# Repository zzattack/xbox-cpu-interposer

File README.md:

# Repository overview
In this repository schematics, layout and gerber files are shared for the recreation of an interposer PCB allowing upgraded Intel CPUs to be used on the original Xbox console. The designs are made in KiCAD.

# Background
Back in 2003 the Taiwanese company FRIENDTECH came up with methods to upgrade computer systems with faster CPUs, and the original Xbox was among the devices for which they offered an upgrade path. Details of their solution can be found in their patent application https://patents.google.com/patent/US20050282621A1/en.

This _interposer board_ follows the same schematic, minus the poorly functioning clock reduction circuitry, and with the BGA footprint positioned to allow use of the original heatsink mounting holes.

# Contact
I can be contacted at frank@zzattack.org if you're looking to obtain PCBs or CPUs.

# Attribution
This board is a recreation of the original FRIENDTECH design. Revision 1 was a board-level clone of original design through intermediate clones by 'trusty', 'N64freak' and 'Kekule'. Revisions 2 and 3 are re-routed from scratch, inspired by pictures of a similar board with cleaner layout by @gaasedelen, who also kindly assisted in finding issues with early board revisions.

# Installation guide
See [guide](https://github.com/zzattack/xbox-cpu-interposer/blob/main/guide.md).

# Status
Full schematic and PCB are routed. Gerber files are available in the Github releases overview.
Revision 3.2 and onwards should be working correctly.
Prior revisions require PCB modifications and should be avoided.

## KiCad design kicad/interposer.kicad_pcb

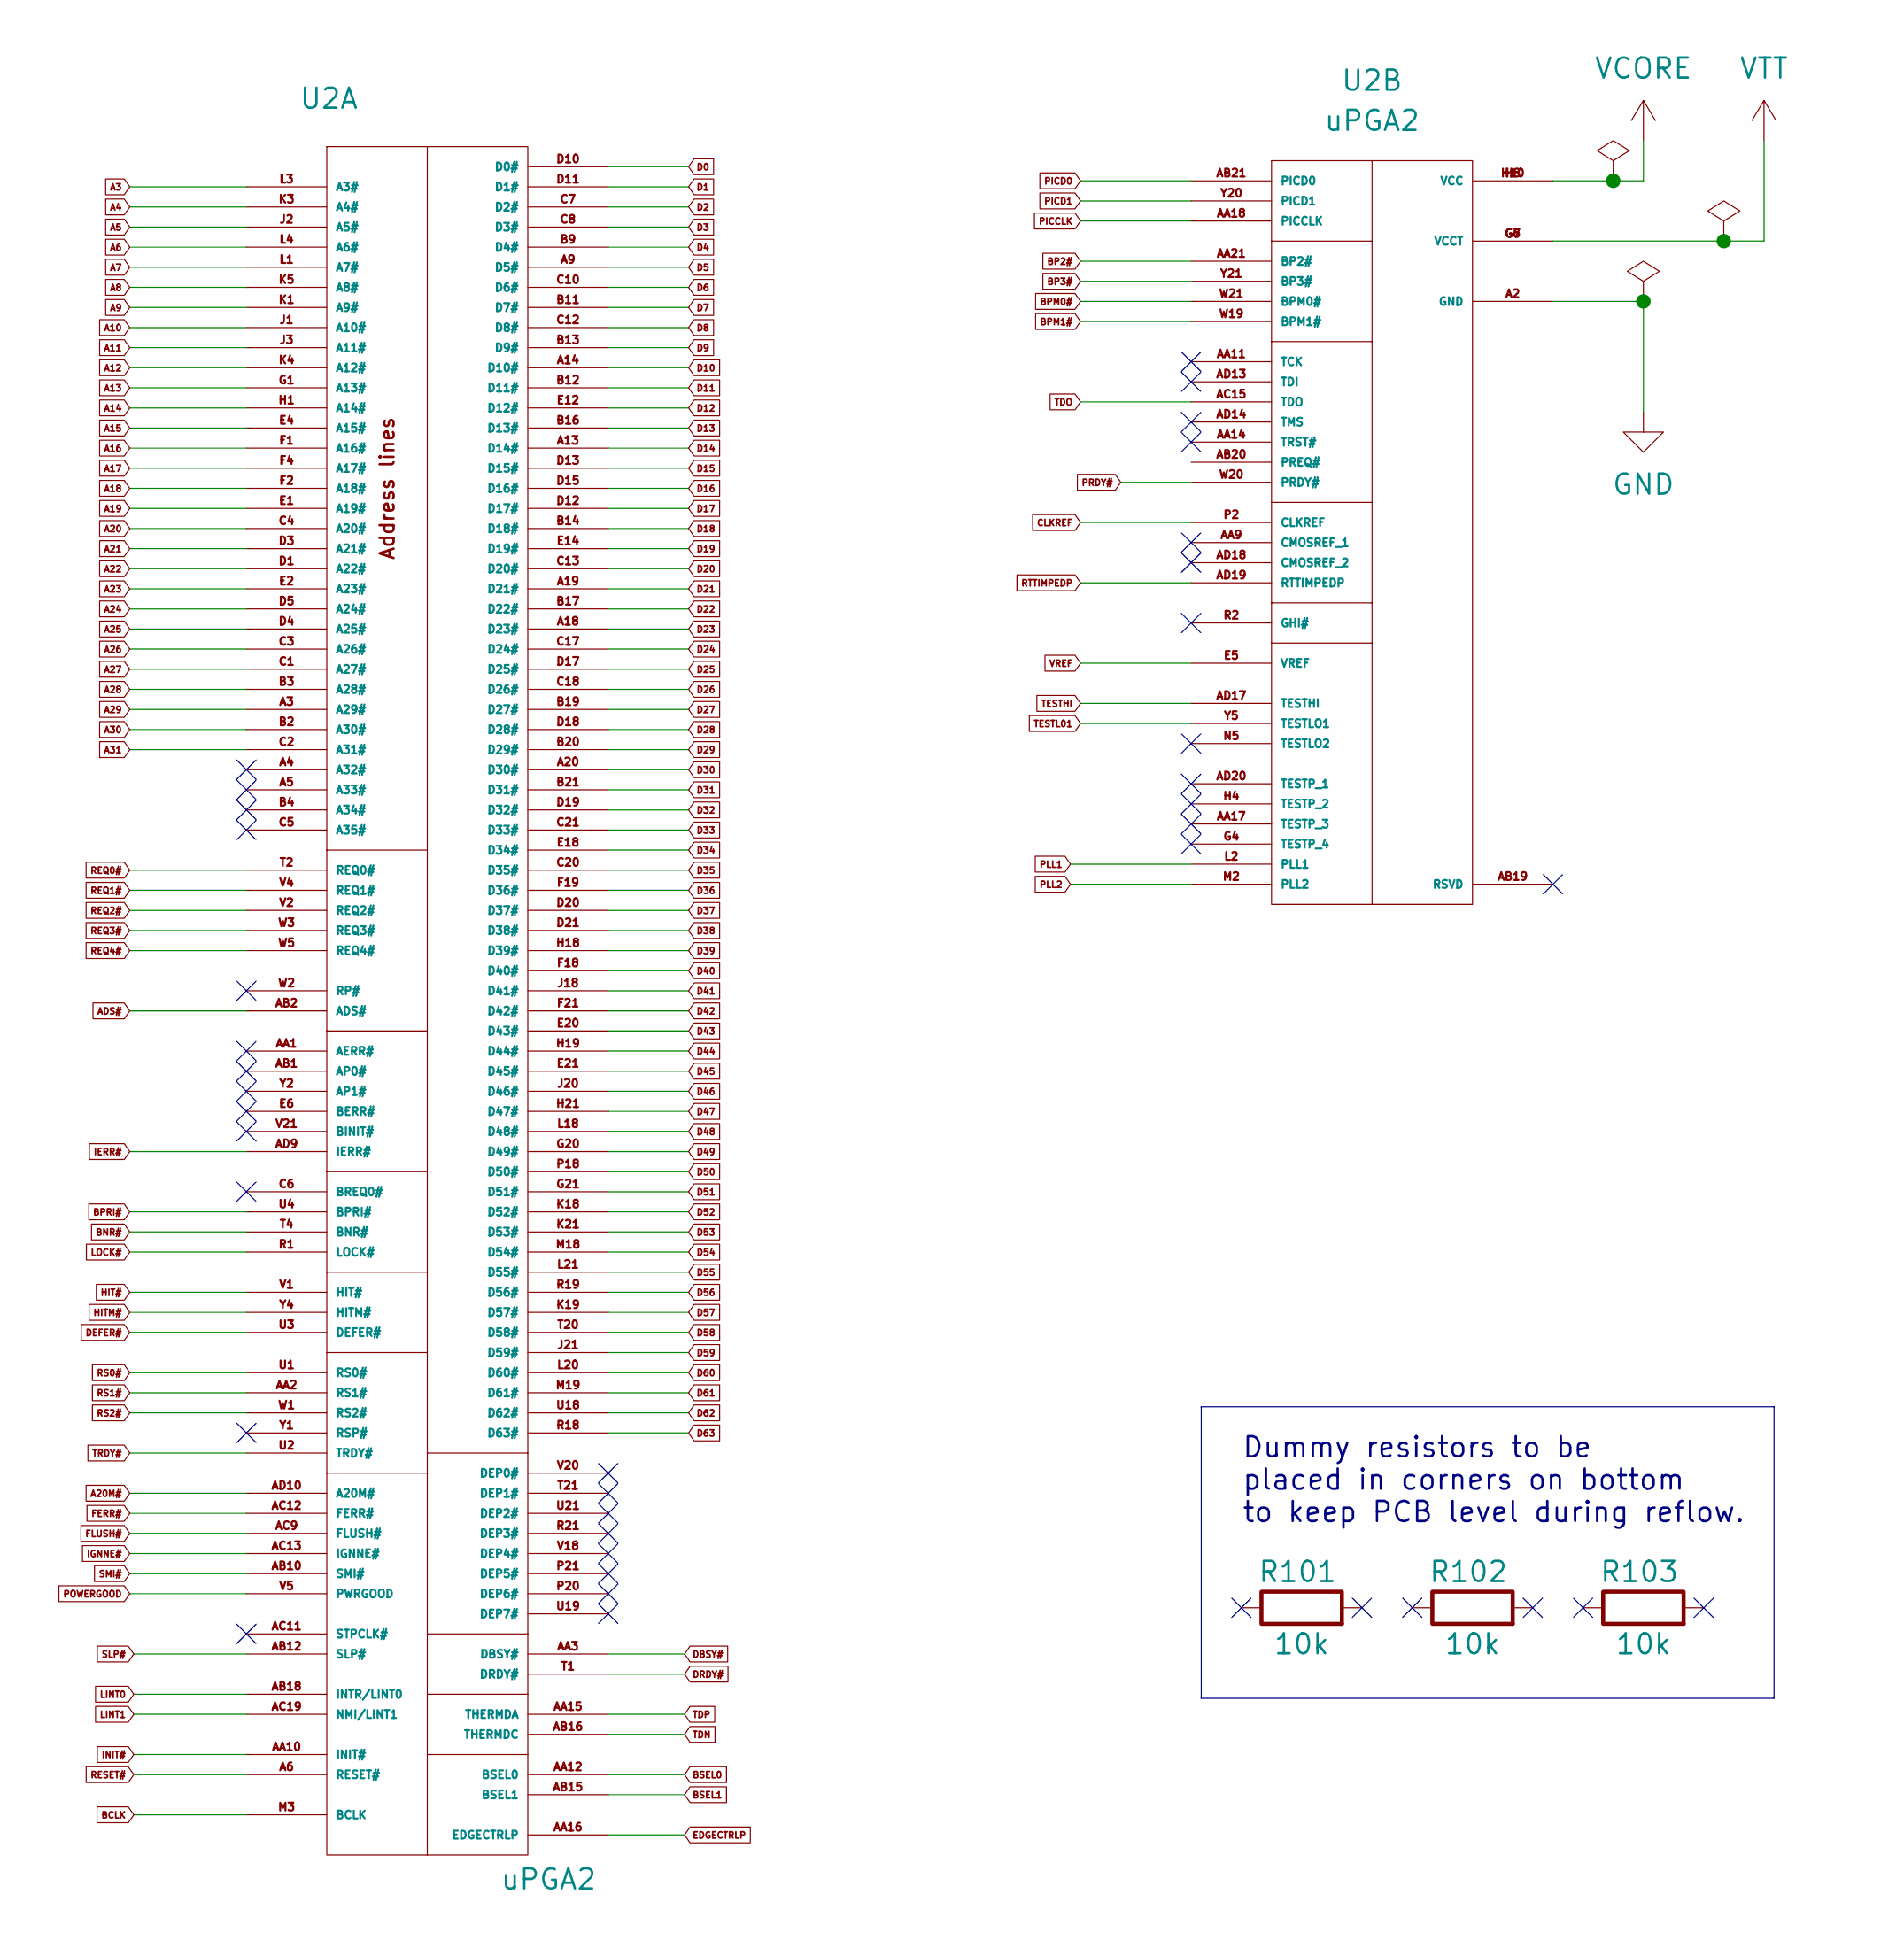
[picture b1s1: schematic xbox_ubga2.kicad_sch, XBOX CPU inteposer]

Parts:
R101, R102, R103: 10k; R_0603_1608Metric
U2: uPGA2; uBGA495-mirrored

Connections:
A3: U2.L3 (A3#); also elsewhere on the board
A4: U2.K3 (A4#); also elsewhere on the board
A5: U2.J2 (A5#); also elsewhere on the board
A6: U2.L4 (A6#); also elsewhere on the board
A7: U2.L1 (A7#); also elsewhere on the board
A8: U2.K5 (A8#); also elsewhere on the board
A9: U2.K1 (A9#); also elsewhere on the board
A10: U2.J1 (A10#); also elsewhere on the board
A11: U2.J3 (A11#); also elsewhere on the board
A12: U2.K4 (A12#); also elsewhere on the board
A13: U2.G1 (A13#); also elsewhere on the board
A14: U2.H1 (A14#); also elsewhere on the board
A15: U2.E4 (A15#); also elsewhere on the board
A16: U2.F1 (A16#); also elsewhere on the board
A17: U2.F4 (A17#); also elsewhere on the board
A18: U2.F2 (A18#); also elsewhere on the board
A19: U2.E1 (A19#); also elsewhere on the board
A20: U2.C4 (A20#); also elsewhere on the board
A20M#: U2.AD10 (A20M#); also elsewhere on the board
A21: U2.D3 (A21#); also elsewhere on the board
A22: U2.D1 (A22#); also elsewhere on the board
A23: U2.E2 (A23#); also elsewhere on the board
A24: U2.D5 (A24#); also elsewhere on the board
A25: U2.D4 (A25#); also elsewhere on the board
A26: U2.C3 (A26#); also elsewhere on the board
A27: U2.C1 (A27#); also elsewhere on the board
A28: U2.B3 (A28#); also elsewhere on the board
A29: U2.A3 (A29#); also elsewhere on the board
A30: U2.B2 (A30#); also elsewhere on the board
A31: U2.C2 (A31#); also elsewhere on the board
ADS#: U2.AB2 (ADS#); also elsewhere on the board
BCLK: U2.M3 (BCLK); also elsewhere on the board
BNR#: U2.T4 (BNR#); also elsewhere on the board
BP2#: U2.AA21 (BP2#); also elsewhere on the board
BP3#: U2.Y21 (BP3#); also elsewhere on the board
BPM0#: U2.W21 (BPM0#); also elsewhere on the board
BPM1#: U2.W19 (BPM1#); also elsewhere on the board
BPRI#: U2.U4 (BPRI#); also elsewhere on the board
BSEL0: U2.AA12 (BSEL0); also elsewhere on the board
BSEL1: U2.AB15 (BSEL1); also elsewhere on the board
CLKREF: U2.P2 (CLKREF); also elsewhere on the board
D0: U2.D10 (D0#); also elsewhere on the board
D1: U2.D11 (D1#); also elsewhere on the board
D2: U2.C7 (D2#); also elsewhere on the board
D3: U2.C8 (D3#); also elsewhere on the board
D4: U2.B9 (D4#); also elsewhere on the board
D5: U2.A9 (D5#); also elsewhere on the board
D6: U2.C10 (D6#); also elsewhere on the board
D7: U2.B11 (D7#); also elsewhere on the board
D8: U2.C12 (D8#); also elsewhere on the board
D9: U2.B13 (D9#); also elsewhere on the board
D10: U2.A14 (D10#); also elsewhere on the board
D11: U2.B12 (D11#); also elsewhere on the board
D12: U2.E12 (D12#); also elsewhere on the board
D13: U2.B16 (D13#); also elsewhere on the board
D14: U2.A13 (D14#); also elsewhere on the board
D15: U2.D13 (D15#); also elsewhere on the board
D16: U2.D15 (D16#); also elsewhere on the board
D17: U2.D12 (D17#); also elsewhere on the board
D18: U2.B14 (D18#); also elsewhere on the board
D19: U2.E14 (D19#); also elsewhere on the board
D20: U2.C13 (D20#); also elsewhere on the board
D21: U2.A19 (D21#); also elsewhere on the board
D22: U2.B17 (D22#); also elsewhere on the board
D23: U2.A18 (D23#); also elsewhere on the board
D24: U2.C17 (D24#); also elsewhere on the board
D25: U2.D17 (D25#); also elsewhere on the board
D26: U2.C18 (D26#); also elsewhere on the board
D27: U2.B19 (D27#); also elsewhere on the board
D28: U2.D18 (D28#); also elsewhere on the board
D29: U2.B20 (D29#); also elsewhere on the board
D30: U2.A20 (D30#); also elsewhere on the board
D31: U2.B21 (D31#); also elsewhere on the board
D32: U2.D19 (D32#); also elsewhere on the board
D33: U2.C21 (D33#); also elsewhere on the board
D34: U2.E18 (D34#); also elsewhere on the board
D35: U2.C20 (D35#); also elsewhere on the board
D36: U2.F19 (D36#); also elsewhere on the board
D37: U2.D20 (D37#); also elsewhere on the board
D38: U2.D21 (D38#); also elsewhere on the board
D39: U2.H18 (D39#); also elsewhere on the board
D40: U2.F18 (D40#); also elsewhere on the board
D41: U2.J18 (D41#); also elsewhere on the board
D42: U2.F21 (D42#); also elsewhere on the board
D43: U2.E20 (D43#); also elsewhere on the board
D44: U2.H19 (D44#); also elsewhere on the board
D45: U2.E21 (D45#); also elsewhere on the board
D46: U2.J20 (D46#); also elsewhere on the board
D47: U2.H21 (D47#); also elsewhere on the board
D48: U2.L18 (D48#); also elsewhere on the board
D49: U2.G20 (D49#); also elsewhere on the board
D50: U2.P18 (D50#); also elsewhere on the board
D51: U2.G21 (D51#); also elsewhere on the board
D52: U2.K18 (D52#); also elsewhere on the board
D53: U2.K21 (D53#); also elsewhere on the board
D54: U2.M18 (D54#); also elsewhere on the board
D55: U2.L21 (D55#); also elsewhere on the board
D56: U2.R19 (D56#); also elsewhere on the board
D57: U2.K19 (D57#); also elsewhere on the board
D58: U2.T20 (D58#); also elsewhere on the board
D59: U2.J21 (D59#); also elsewhere on the board
D60: U2.L20 (D60#); also elsewhere on the board
D61: U2.M19 (D61#); also elsewhere on the board
D62: U2.U18 (D62#); also elsewhere on the board
D63: U2.R18 (D63#); also elsewhere on the board
DBSY#: U2.AA3 (DBSY#); also elsewhere on the board
DEFER#: U2.U3 (DEFER#); also elsewhere on the board
DRDY#: U2.T1 (DRDY#); also elsewhere on the board
EDGECTRLP: U2.AA16 (EDGECTRLP); also elsewhere on the board
FERR#: U2.AC12 (FERR#); also elsewhere on the board
FLUSH#: U2.AC9 (FLUSH#); also elsewhere on the board
GND: U2.A2 (GND), U2.A7 (GND), U2.A8 (GND), U2.A12 (GND), U2.A21 (GND), U2.AA4 (GND), U2.AA13 (GND), U2.AA20 (GND), U2.AB3 (GND), U2.AB5 (GND), U2.AB9 (GND), U2.AB11 (GND), U2.AB13 (GND), U2.AB14 (GND), U2.AB17 (GND), U2.AC1 (GND), U2.AC2 (GND), U2.AC5 (GND), U2.AC10 (GND), U2.AC14 (GND), U2.AC16 (GND), U2.AC18 (GND), U2.AC21 (GND), U2.AD1 (GND), U2.AD5 (GND), U2.AD16 (GND), U2.AD21 (GND), U2.B1 (GND), U2.B5 (GND), U2.B6 (GND), U2.B7 (GND), U2.B8 (GND), U2.B10 (GND), U2.B15 (GND), U2.B18 (GND), U2.C9 (GND), U2.C11 (GND), U2.C15 (GND), U2.C16 (GND), U2.C19 (GND), U2.D2 (GND), U2.D6 (GND), U2.D7 (GND), U2.D9 (GND), U2.E3 (GND), U2.E7 (GND), U2.E8 (GND), U2.E9 (GND), U2.E10 (GND), U2.E11 (GND), U2.E13 (GND), U2.E19 (GND), U2.F3 (GND), U2.F6 (GND), U2.F7 (GND), U2.F8 (GND), U2.F9 (GND), U2.F10 (GND), U2.F11 (GND), U2.F12 (GND), U2.F13 (GND), U2.F14 (GND), U2.F15 (GND), U2.F16 (GND), U2.F20 (GND), U2.G3 (GND), U2.G19 (GND), U2.H2 (GND), U2.H7 (GND), U2.H9 (GND), U2.H11 (GND), U2.H13 (GND), U2.H15 (GND), U2.H20 (GND), U2.J4 (GND), U2.J8 (GND), U2.J10 (GND), U2.J12 (GND), U2.J14 (GND), U2.J16 (GND), U2.J19 (GND), U2.K2 (GND), U2.K7 (GND), U2.K9 (GND), U2.K11 (GND), U2.K13 (GND), U2.K15 (GND), U2.K20 (GND), U2.L5 (GND), U2.L8 (GND), U2.L10 (GND), U2.L12 (GND), U2.L14 (GND), U2.L16 (GND), U2.L19 (GND), U2.M7 (GND), U2.M9 (GND), U2.M11 (GND), U2.M13 (GND), U2.M15 (GND), U2.M20 (GND), U2.N2 (GND), U2.N3 (GND), U2.N4 (GND), U2.N8 (GND), U2.N10 (GND), U2.N12 (GND), U2.N14 (GND), U2.N16 (GND), U2.N18 (GND), U2.N19 (GND), U2.N20 (GND), U2.P5 (GND), U2.P7 (GND), U2.P9 (GND), U2.P11 (GND), U2.P13 (GND), U2.P15 (GND), U2.P19 (GND), U2.R3 (GND), U2.R4 (GND), U2.R5 (GND), U2.R8 (GND), U2.R10 (GND), U2.R12 (GND), U2.R14 (GND), U2.R16 (GND), U2.R20 (GND), U2.T3 (GND), U2.T5 (GND), U2.T7 (GND), U2.T9 (GND), U2.T11 (GND), U2.T13 (GND), U2.T15 (GND), U2.T18 (GND), U2.T19 (GND), U2.U8 (GND), U2.U10 (GND), U2.U12 (GND), U2.U14 (GND), U2.U16 (GND), U2.U20 (GND), U2.V3 (GND), U2.V19 (GND), U2.W4 (GND), U2.W18 (GND), U2.Y3 (GND), U2.Y9 (GND), U2.Y10 (GND), U2.Y11 (GND), U2.Y12 (GND), U2.Y13 (GND), U2.Y14 (GND), U2.Y15 (GND), U2.Y16 (GND), U2.Y19 (GND); also elsewhere on the board
HIT#: U2.V1 (HIT#); also elsewhere on the board
HITM#: U2.Y4 (HITM#); also elsewhere on the board
IERR#: U2.AD9 (IERR#); also elsewhere on the board
IGNNE#: U2.AC13 (IGNNE#); also elsewhere on the board
INIT#: U2.AA10 (INIT#); also elsewhere on the board
LINT0: U2.AB18 (INTR/LINT0); also elsewhere on the board
LINT1: U2.AC19 (NMI/LINT1); also elsewhere on the board
LOCK#: U2.R1 (LOCK#); also elsewhere on the board
PICCLK: U2.AA18 (PICCLK); also elsewhere on the board
PICD0: U2.AB21 (PICD0); also elsewhere on the board
PICD1: U2.Y20 (PICD1); also elsewhere on the board
PLL1: U2.L2 (PLL1); also elsewhere on the board
PLL2: U2.M2 (PLL2); also elsewhere on the board
POWERGOOD: U2.V5 (PWRGOOD); also elsewhere on the board
PRDY#: U2.W20 (PRDY#); also elsewhere on the board
REQ0#: U2.T2 (REQ0#); also elsewhere on the board
REQ1#: U2.V4 (REQ1#); also elsewhere on the board
REQ2#: U2.V2 (REQ2#); also elsewhere on the board
REQ3#: U2.W3 (REQ3#); also elsewhere on the board
REQ4#: U2.W5 (REQ4#); also elsewhere on the board
RESET#: U2.A6 (RESET#); also elsewhere on the board
RS0#: U2.U1 (RS0#); also elsewhere on the board
RS1#: U2.AA2 (RS1#); also elsewhere on the board
RS2#: U2.W1 (RS2#); also elsewhere on the board
RTTIMPEDP: U2.AD19 (RTTIMPEDP); also elsewhere on the board
SLP#: U2.AB12 (SLP#); also elsewhere on the board
SMI#: U2.AB10 (SMI#); also elsewhere on the board
TDN: U2.AB16 (THERMDC); also elsewhere on the board
TDO: U2.AC15 (TDO); also elsewhere on the board
TDP: U2.AA15 (THERMDA); also elsewhere on the board
TESTHI: U2.AD17 (TESTHI); also elsewhere on the board
TESTL01: U2.Y5 (TESTLO1); also elsewhere on the board
TRDY#: U2.U2 (TRDY#); also elsewhere on the board
VCORE: U2.H8 (VCC), U2.H10 (VCC), U2.H12 (VCC), U2.H14 (VCC), U2.H16 (VCC), U2.J7 (VCC), U2.J9 (VCC), U2.J11 (VCC), U2.J13 (VCC), U2.J15 (VCC), U2.K8 (VCC), U2.K10 (VCC), U2.K12 (VCC), U2.K14 (VCC), U2.K16 (VCC), U2.L7 (VCC), U2.L9 (VCC), U2.L11 (VCC), U2.L13 (VCC), U2.L15 (VCC), U2.M8 (VCC), U2.M10 (VCC), U2.M12 (VCC), U2.M14 (VCC), U2.M16 (VCC), U2.N7 (VCC), U2.N9 (VCC), U2.N11 (VCC), U2.N13 (VCC), U2.N15 (VCC), U2.P1 (VCC), U2.P8 (VCC), U2.P10 (VCC), U2.P12 (VCC), U2.P14 (VCC), U2.P16 (VCC), U2.R7 (VCC), U2.R9 (VCC), U2.R11 (VCC), U2.R13 (VCC), U2.R15 (VCC), U2.T8 (VCC), U2.T10 (VCC), U2.T12 (VCC), U2.T14 (VCC), U2.T16 (VCC), U2.U7 (VCC), U2.U9 (VCC), U2.U11 (VCC), U2.U13 (VCC), U2.U15 (VCC); also elsewhere on the board
VREF: U2.E5 (VREF), U2.E16 (VREF), U2.E17 (VREF), U2.F5 (VREF), U2.F17 (VREF), U2.U5 (VREF), U2.Y17 (VREF), U2.Y18 (VREF); also elsewhere on the board
VTT: U2.AA6 (VCCT), U2.AA7 (VCCT), U2.AA8 (VCCT), U2.AB6 (VCCT), U2.AB7 (VCCT), U2.AB8 (VCCT), U2.AC6 (VCCT), U2.AC7 (VCCT), U2.AC8 (VCCT), U2.AD6 (VCCT), U2.AD7 (VCCT), U2.AD8 (VCCT), U2.G6 (VCCT), U2.G7 (VCCT), U2.G8 (VCCT), U2.G9 (VCCT), U2.G10 (VCCT), U2.G11 (VCCT), U2.G12 (VCCT), U2.G13 (VCCT), U2.G14 (VCCT), U2.G15 (VCCT), U2.G16 (VCCT), U2.G17 (VCCT), U2.H6 (VCCT), U2.H17 (VCCT), U2.J6 (VCCT), U2.J17 (VCCT), U2.K6 (VCCT), U2.K17 (VCCT), U2.L6 (VCCT), U2.L17 (VCCT), U2.M6 (VCCT), U2.M17 (VCCT), U2.N6 (VCCT), U2.N17 (VCCT), U2.P6 (VCCT), U2.P17 (VCCT), U2.R6 (VCCT), U2.R17 (VCCT), U2.T6 (VCCT), U2.T17 (VCCT), U2.U6 (VCCT), U2.U17 (VCCT), U2.V6 (VCCT), U2.V7 (VCCT), U2.V8 (VCCT), U2.V9 (VCCT), U2.V10 (VCCT), U2.V11 (VCCT), U2.V12 (VCCT), U2.V13 (VCCT), U2.V14 (VCCT), U2.V15 (VCCT), U2.V16 (VCCT), U2.V17 (VCCT), U2.W6 (VCCT), U2.W7 (VCCT), U2.W8 (VCCT), U2.W9 (VCCT), U2.W10 (VCCT), U2.W11 (VCCT), U2.W12 (VCCT), U2.W13 (VCCT), U2.W14 (VCCT), U2.W15 (VCCT), U2.W16 (VCCT), U2.W17 (VCCT), U2.Y6 (VCCT), U2.Y7 (VCCT), U2.Y8 (VCCT); also elsewhere on the board

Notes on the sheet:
Dummy resistors to be placed in corners on bottom to keep PCB level during reflow.
